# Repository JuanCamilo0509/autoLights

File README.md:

# Automatic light module
This project aims to be a plug and play wall switch based on the esp8266 board and using MQTT protocol for communications.

```
.
├── Hardware
│   └── autoLightPCB(Kicad)
├── README.md
└── software
    ├── lightModule(esp8266)
    └── mosquittoServer
        └── mosquitto.conf
```

This project has two main directories:
    - Software: Two main sub-directories, the light-Module where the code for the esp is maintain, and the "mosquitto-Server" with the ".conf" file for the server. 
    - Hardware: In this repository you can find the PCB layout for the board and the 3d model for the case.
## How to configure an ESP?
1. Upload the code to the esp.
2. When power, the esp will create a WIFI entrance call "esp".
3. Connect to "esp" Network.
4. Using any browser go to `htpp://192.168.4.1/`.
5. Fill all the information for the esp. (You can test the light to know which light you're setting up).
6. Send all the information. The esp should restart with all the information saved.
7. You're done, try to change the state from your phone. (I recommend using IoT MQTT Panel to test it).

## Features
- HTTP Server on SoftAP mode when the variables aren't on the esp memory to set them up: (SSID, WiFi password, broker and topic).
<table>
  <tr>
    <td>
      
    </td>
    <td>
      
    </td>
  </tr>
</table>

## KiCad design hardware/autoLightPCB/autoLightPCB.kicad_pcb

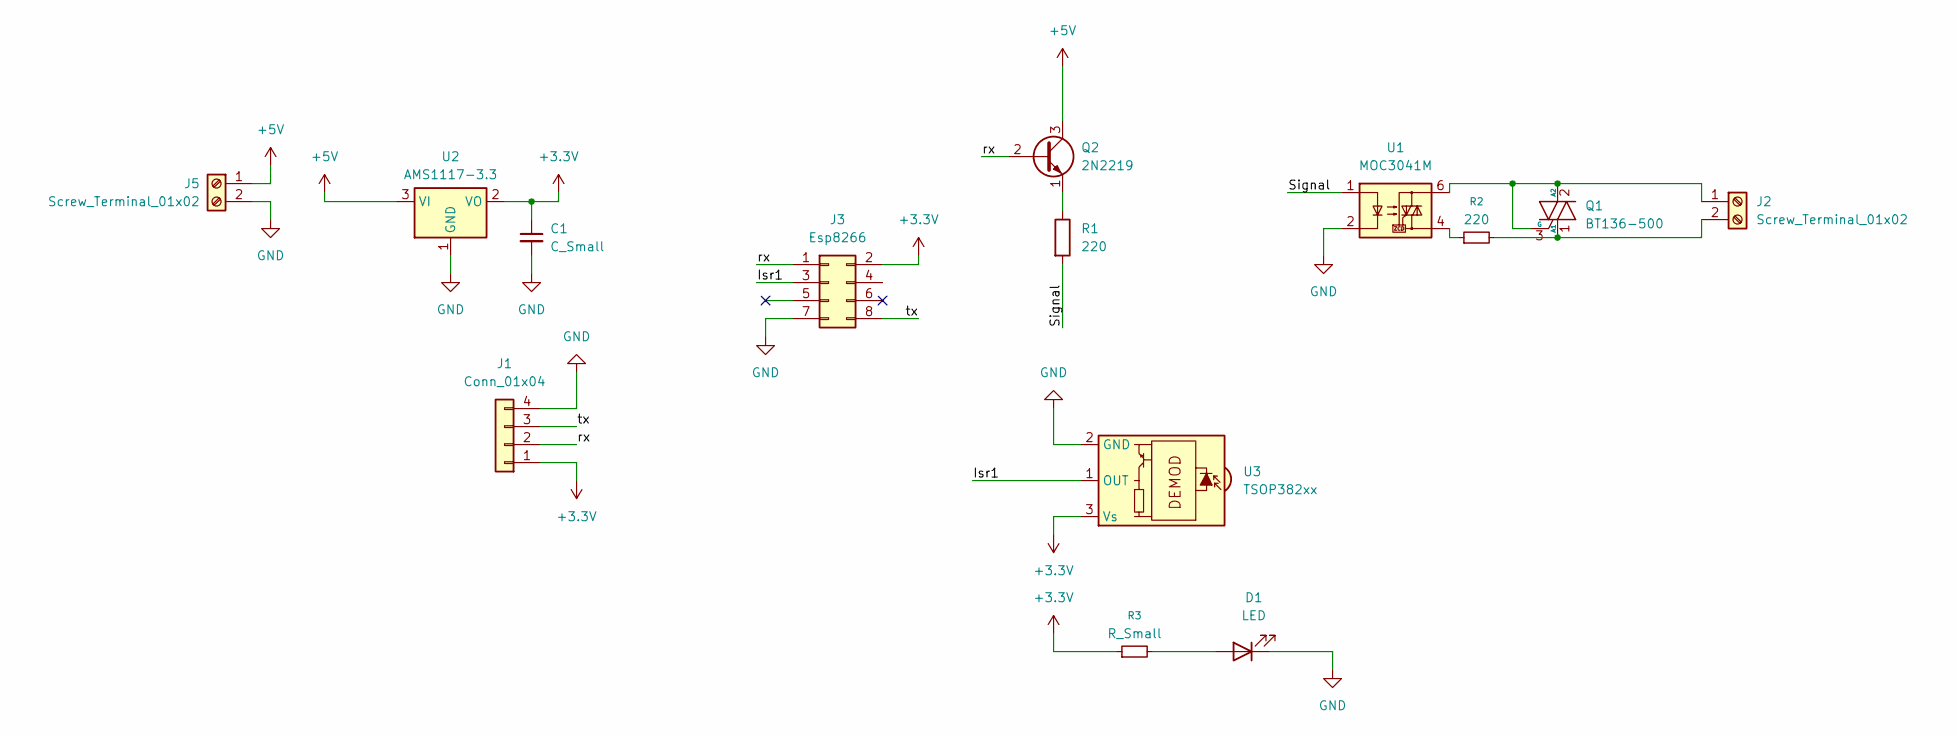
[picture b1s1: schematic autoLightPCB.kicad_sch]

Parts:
C1: C_Small; C_0504_1310Metric
D1: LED; LED_D5.0mm
J1: Conn_01x04; PinHeader_1x04_P1.27mm_Vertical
J2, J5: Screw_Terminal_01x02; PhoenixContact_SPT_1.5_2-H-3.5_1x02_P3.5mm_Horizontal
J3: Esp8266; Wuerth_WR-PHD_613008216921_Large_2x04_P2.54mm_Vertical
Q1: BT136-500; TO-220-3_Vertical
Q2: 2N2219; TO-92L_Inline
R1, R2: 220; R_0603_1608Metric
R3: R_Small; R_0603_1608Metric
U1: MOC3041M; DIP-6_W7.62mm_LongPads
U2: AMS1117-3.3; SOT-223-3_TabPin2
U3: TSOP382xx; Vishay_MINICAST-3Pin

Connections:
+3.3V: C1.1, J1.1, J3.2, R3.1, U2.2 (VO), U3.3 (Vs)
+5V: J5.1, Q2.3 (C), U2.3 (VI)
/Isr1: J3.3, U3.1 (OUT)
/Signal: R1.2, U1.1
/rx: J1.2, J3.1, Q2.2 (B)
/tx: J1.3, J3.8
GND: C1.2, D1.1 (K), J1.4, J3.7, J5.2, U1.2, U2.1 (GND), U3.2 (GND)
unnamed: D1.2 (A), R3.2
unnamed: J2.1, Q1.2 (A2), Q1.3 (G), U1.6
unnamed: J2.2, Q1.1 (A1), R2.2
unnamed: Q2.1 (E), R1.1
unnamed: R2.1, U1.4

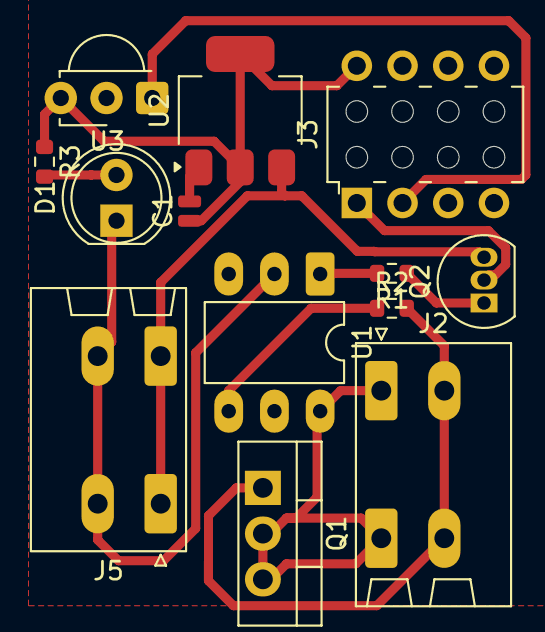
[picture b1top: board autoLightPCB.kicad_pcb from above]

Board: 2 copper layers, 13 parts (0 on the bottom side), 11 nets.

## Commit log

2026-04-11 Main functionality (pcb and esp code).
2026-04-11 Modifying README files.
2026-04-11 mod README SOFTWARE
2026-04-11 adding future features on the README file
2026-04-12 Adding the server functionality on first boot.
2026-04-12 Enhance README with images and feature descriptions
    Added images to the README for visual representation of features.
2026-04-12 Add ISR to erase ESP memory (factory reset)
    - Added FACTORY_RESET_GPIO definition (GPIO3/RX pin)
    - Created factory_reset_isr_handler() to restart ESP
    - Added initialize_factory_reset_gpio() to configure the ISR
    - ISR triggers on negative edge (button press to ground)
    - Users can now reset device to factory settings by grounding GPIO3
2026-04-12 Fix test light button
    - Add POST /test endpoint to toggle GPIO2 light state
    - Include gpio.h header for light control functions
    - Update HTML button to use fetch POST instead of location redirect
    - Add status feedback to show light state after toggle
    Fixes #1
2026-04-12 Fix: Add POST handler for test button to toggle GPIO2
    - Added post_handler_test() function that toggles the light state
    - Updated form page to use POST method for test button (was onclick navigate)
    - Registered /test POST endpoint in start_webserver()
    - Includes gpio.h header for update_light_state() and get_light_state() functions
    Fixes #1
2026-04-12 Fix #2. Creating a new ISR on gpio5 to erase nvs. Using gpio5 to reset when the user wants to reconfigurated the esp.
2026-04-13 Fix #1. Fixing the button to change light state. Deleting the webPage.
2026-04-13 ReadME update: How to configure the esp.
